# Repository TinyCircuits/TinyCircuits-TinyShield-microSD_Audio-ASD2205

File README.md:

# TinyCircuits TinyShield microSD and Audio Adapter Board - ASD2205 Rev3

The design files are located under design_files/ for the TinyCircuits ASD2205 Rev 3 PCB.  This is a TinyShield board that has a microSD connector, local power supply and level shifters to connect to a microSD card and an audio amplifier.

Format is in Cadsoft Eagle format - Eagle version 6.2 was used for the original design.

For more infomation on this, check out the product page at TinyCircuits.com:  https://tinycircuits.com/products/microsd-tinyshield

# License:

Design by TinyCircuits.
All design files are released under the Creative Commons Attribution Share-Alike 3.0 License, see the following link for details: http://creativecommons.org/licenses/by-sa/3.0

All text above must be included in any redistribution or derived design

This project uses designs and concepts developed as part of the Arduino project and the LilyPad project.  The TinyCircuits design files themselves (schematics, PCB and libraries) are not directly derived from these works' design files and have been created new, however the concepts and basic architecture behind the TinyDuino and TinyLily products are derived and we thank the hard work of the organizations below for their contributions to open-source hardware:
  
Original Arduino Uno Design by Team Arduino

LilyPad Arduino Design by Leah Buechley and Sparkfun Electronics

Please support the open-source hardware community

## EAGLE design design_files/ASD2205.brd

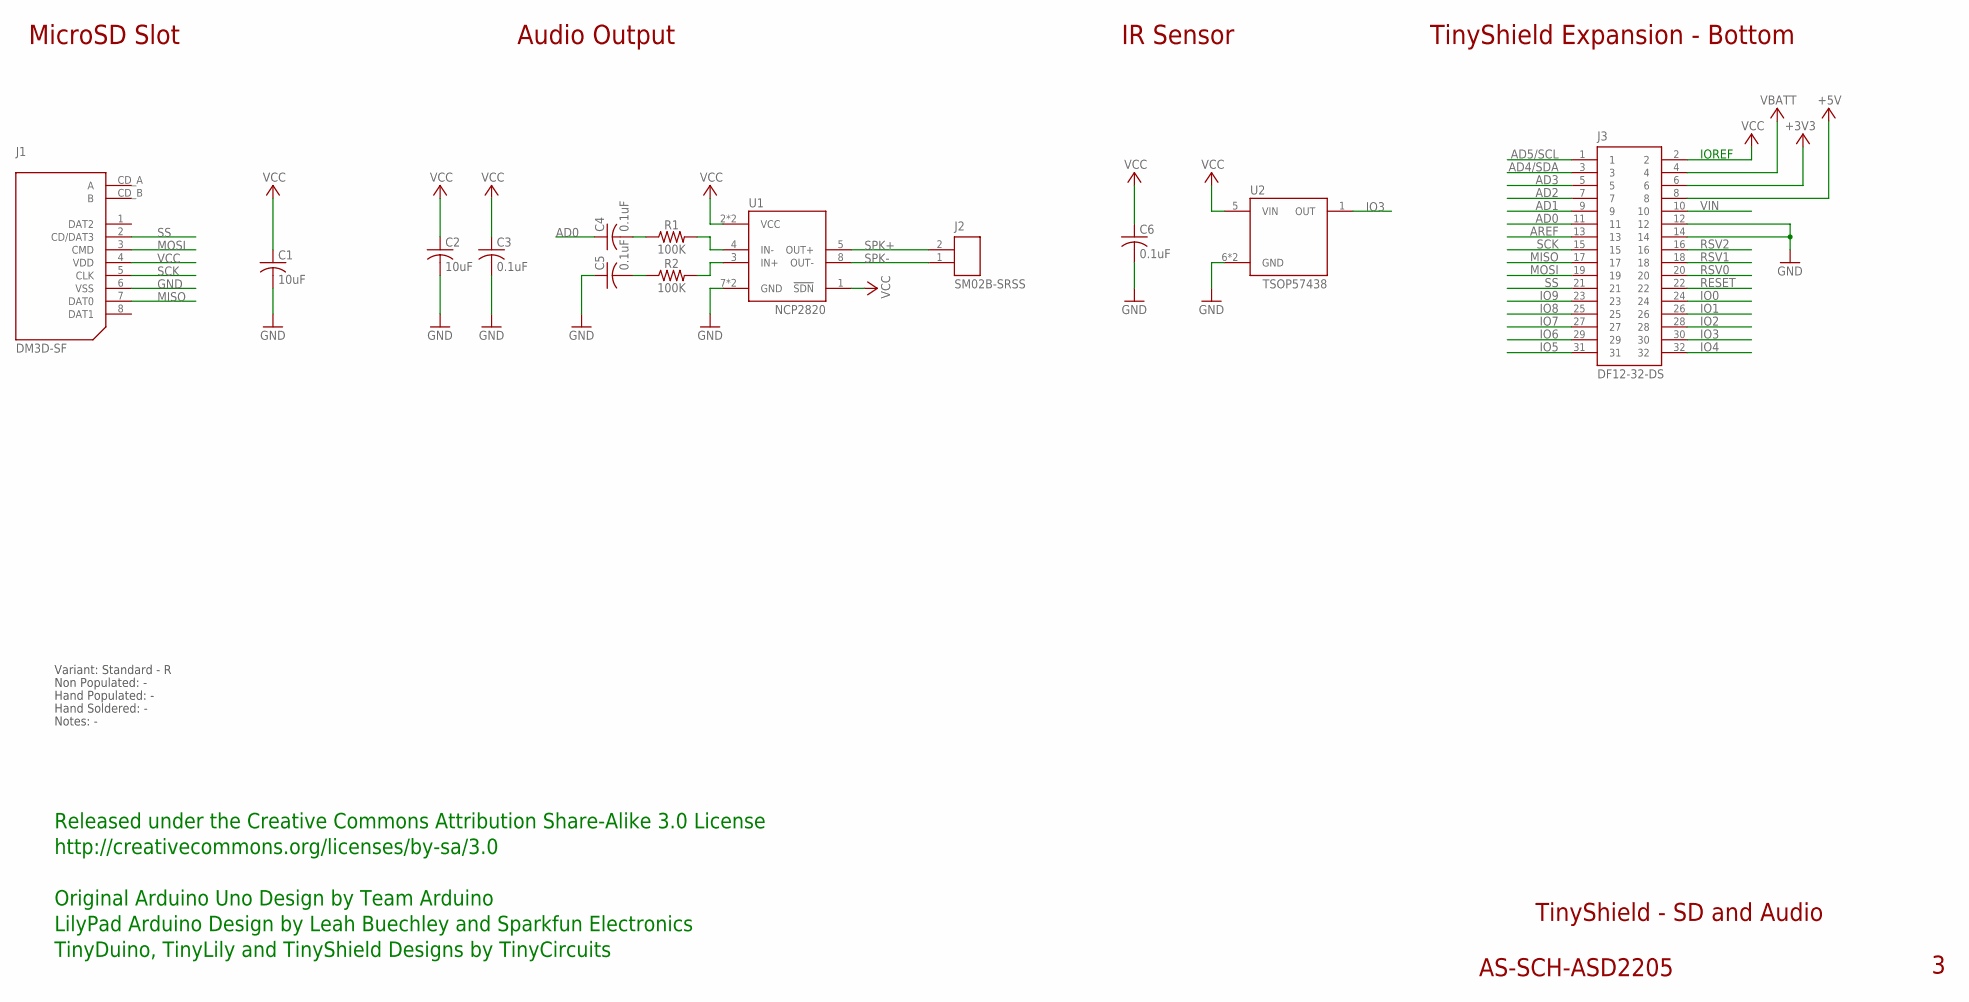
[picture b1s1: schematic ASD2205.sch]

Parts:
C1: 10uF; C0603
C2: 10uF; C0603; PARTNO AS-ITM-00002
C3, C4, C5, C6: 0.1uF; C0402
J1: DM3D-SF; SD_CARD
J2: SM02B-SRSS; JST_SH_2X1
J3: DF12-32-DS; PARTNO AS-ITM-00012
R1, R2: 100K; 0402
U1: NCP2820; WSON-8
U2: TSOP57438; TSOP57

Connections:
+3V3: J3.6
+5V: J3.8
AD0: C4.1, J3.11
AD1: J3.9
AD2: J3.7
AD3: J3.5
AD4/SDA: J3.3
AD5/SCL: J3.1
AREF: J3.13
GND: C1.2, C2.2, C3.2, C5.1, C6.2, J1.6 (VSS), J3.12, J3.14, U1.7 (GND), U1.9 (GND), U2.6 (GND), U2.8 (GND)
IO0: J3.24
IO1: J3.26
IO2: J3.28
IO3: J3.30, U2.1 (OUT)
IO4: J3.32
IO5: J3.31
IO6: J3.29
IO7: J3.27
IO8: J3.25
IO9: J3.23
MISO: J1.7 (DAT0), J3.17
MOSI: J1.3 (CMD), J3.19
unnamed: R1.2, U1.4 (IN-)
unnamed: R2.2, U1.3 (IN+)
unnamed: C4.2, R1.1
unnamed: C5.2, R2.1
RESET: J3.22
RSV0: J3.20
RSV1: J3.18
RSV2: J3.16
SCK: J1.5 (CLK), J3.15
SPK+: J2.2 (1), U1.5 (OUT+)
SPK-: J2.1 (2), U1.8 (OUT-)
SS: J1.2 (CD/DAT3), J3.21
VBATT: J3.4
VCC: C1.1, C2.1, C3.1, C6.1, J1.4 (VDD), J3.2, U1.1 (!SDN), U1.2 (VCC), U1.6 (VCC), U2.5 (VIN)
VIN: J3.10

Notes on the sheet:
TinyShield Expansion - Bottom
TinyShield - SD and Audio
AS-SCH-ASD2205
IOREF
Released under the Creative Commons Attribution Share-Alike 3.0 License
http://creativecommons.org/licenses/by-sa/3.0
LilyPad Arduino Design by Leah Buechley and Sparkfun Electronics
TinyDuino, TinyLily and TinyShield Designs by TinyCircuits
Original Arduino Uno Design by Team Arduino
IR Sensor
Audio Output
MicroSD Slot
Non Populated: -
Hand Populated: -
Hand Soldered: -
Notes: -
Variant: Standard - R

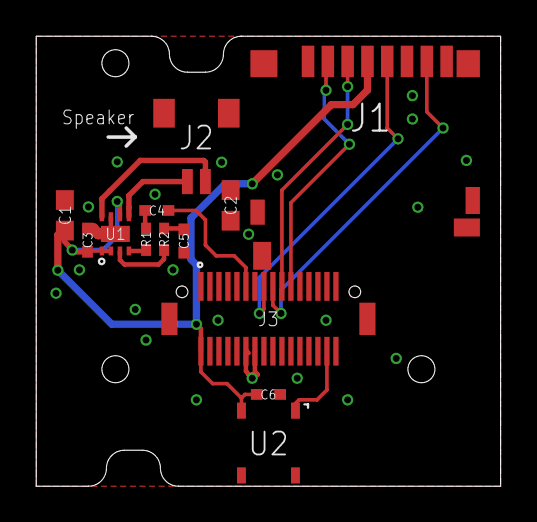
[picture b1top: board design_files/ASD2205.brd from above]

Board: 2 copper layers, 25.8 x 25.0 mm, 14 parts (0 on the bottom side), 14 nets.

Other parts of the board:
U$1: DOCFIELD-TINYCIRCUITS-PCB

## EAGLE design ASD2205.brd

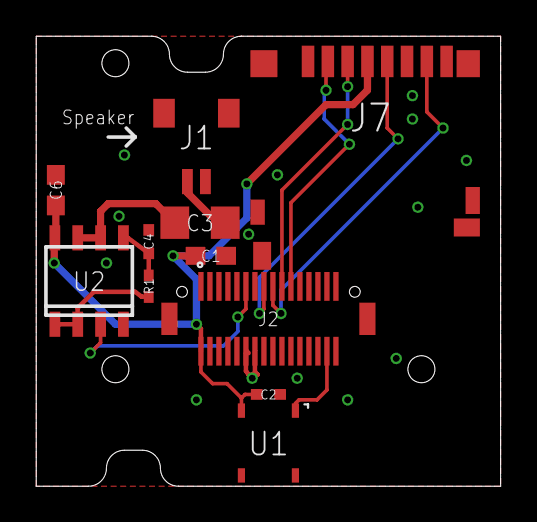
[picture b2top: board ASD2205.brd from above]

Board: 2 copper layers, 25.8 x 25.0 mm, 12 parts (0 on the bottom side), 12 nets.

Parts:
C1, C6: 10uF; C0603
C2: 0.1uF; C0402
C3: 100uF; C1206
C4: 10nF; C0402
J1: SM02B-SRSS; JST_SH_2X1
J2: DF12-32-DS
J7: DM3D-SF; SD_CARD
R1: 1.00K; 0402
U1: TSOP57438; TSOP57
U2: TS922IDT; SO-08-COMPACT
U$1: DOCFIELD-TINYCIRCUITS-PCB

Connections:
AD0: J2.11, U2.3
GND: C1.2, C2.2, C4.2, C6.2, J1.1, J2.12, J2.14, J7.6, U1.6, U1.8, U2.4
IO3: J2.30, U1.1
MISO: J2.17, J7.7
MOSI: J2.19, J7.3
unnamed: C3.1, U2.6, U2.7
unnamed: C3.2, J1.2
unnamed: C4.1, R1.2, U2.5
unnamed: R1.1, U2.1, U2.2
SCK: J2.15, J7.5
SS: J2.21, J7.2
VCC: C1.1, C2.1, C6.1, J2.2, J7.4, U1.5, U2.8

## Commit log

2019-01-04 change format
2019-01-07 updated comments
2019-05-22 added images
2019-05-24 edit image
2019-05-24 pics
2019-05-31 updated images
2020-02-11 image update
2020-07-28 Add CAD data
2020-08-14 Update CAD drawing
2022-02-22 Update hardware rev
